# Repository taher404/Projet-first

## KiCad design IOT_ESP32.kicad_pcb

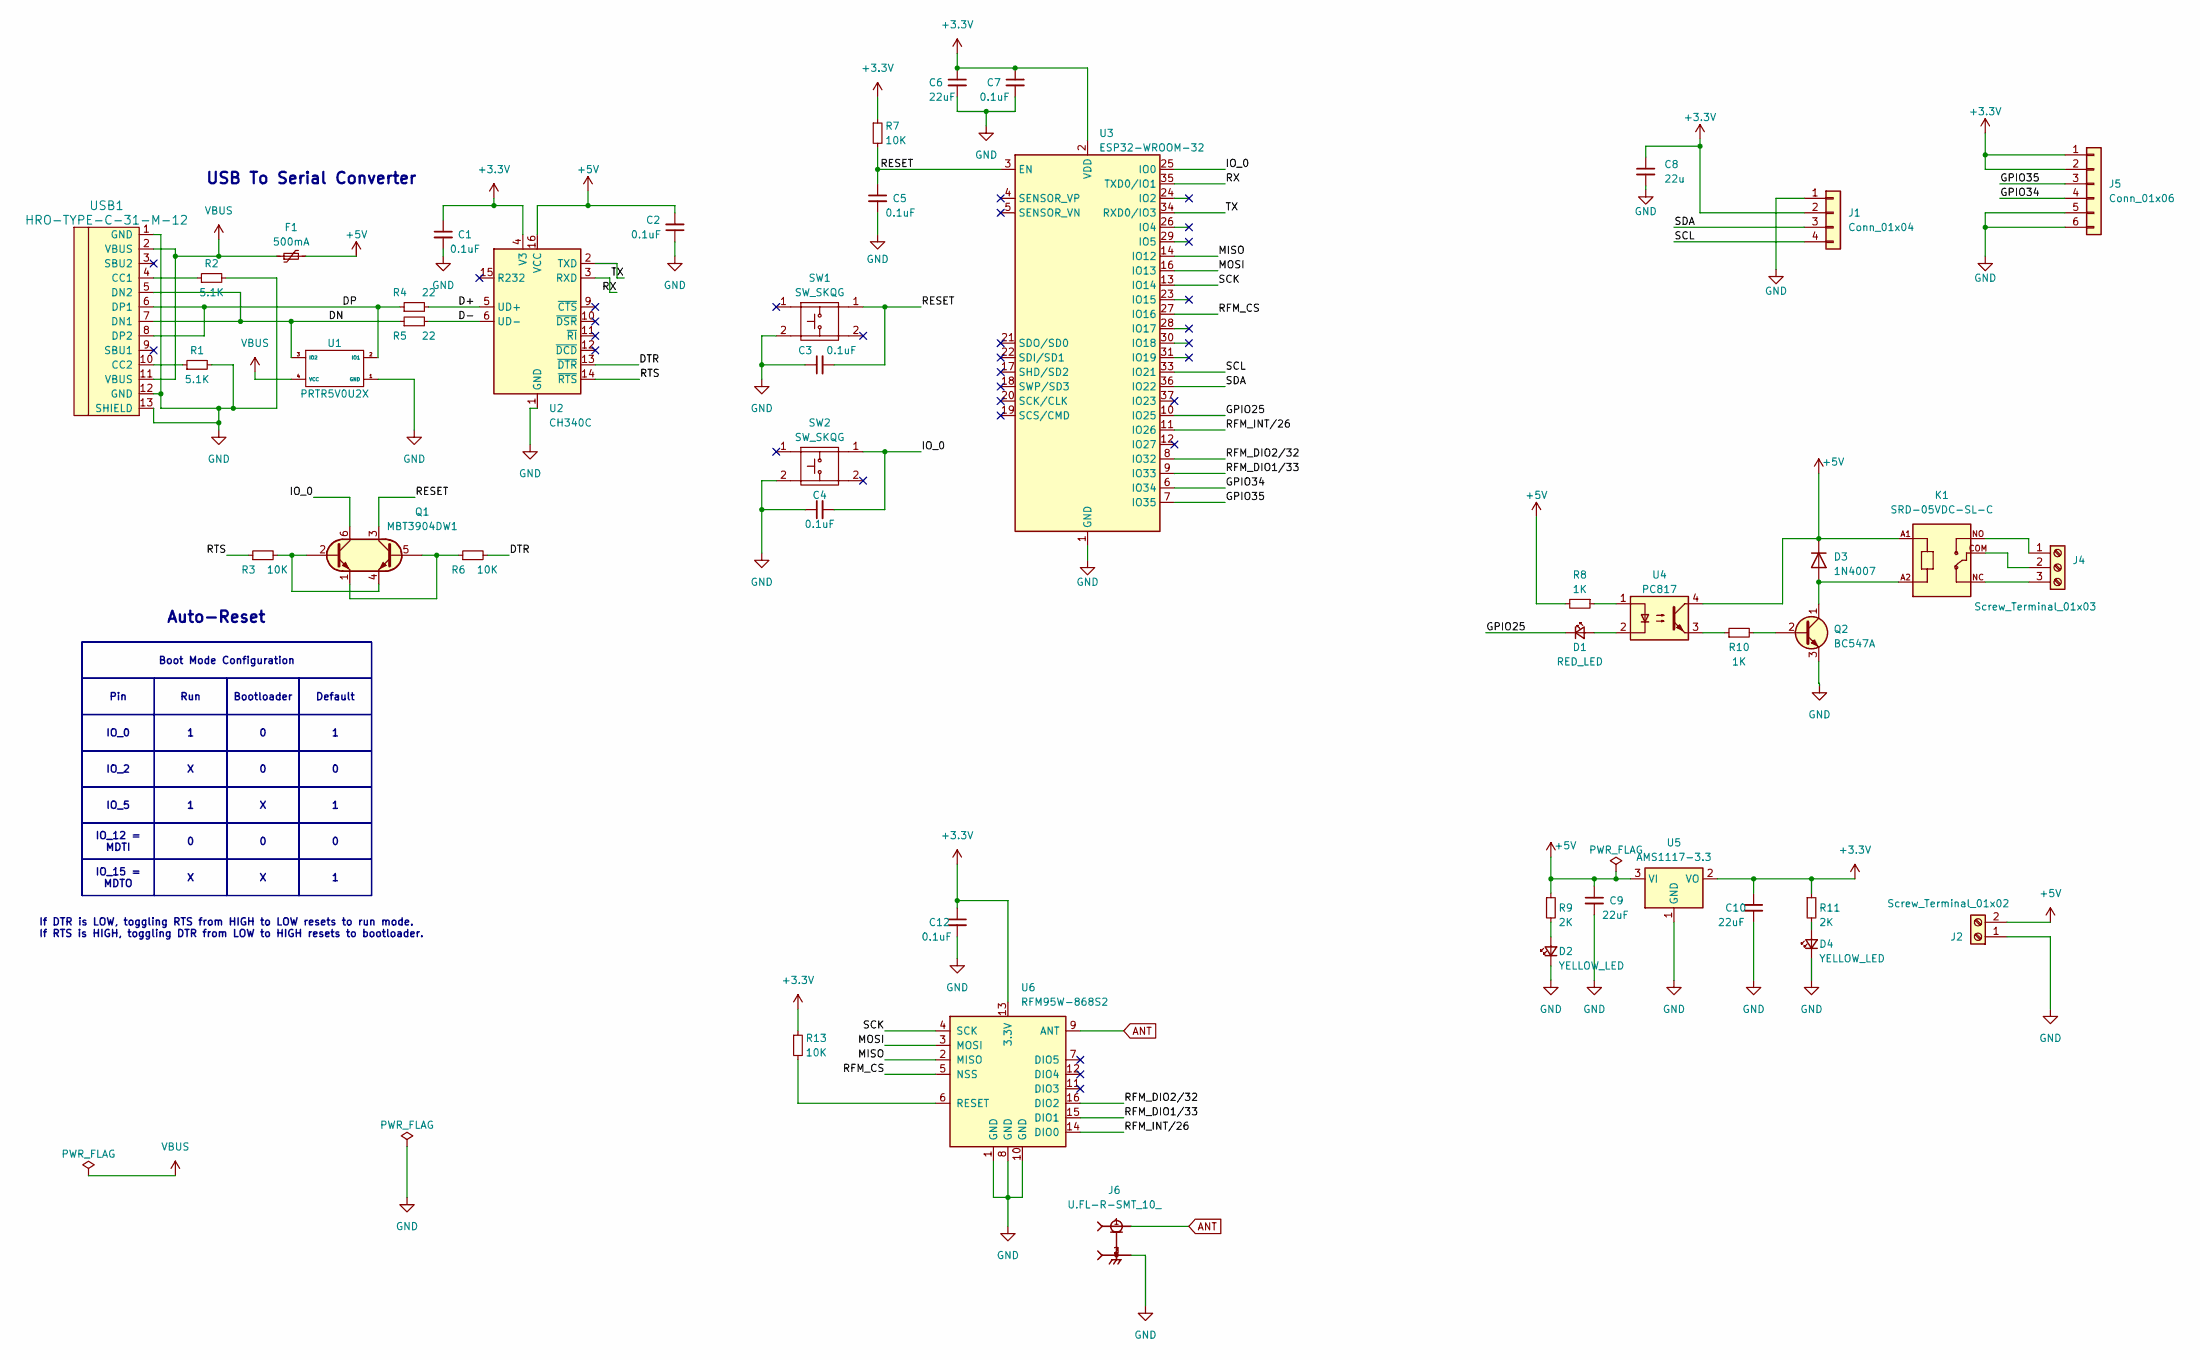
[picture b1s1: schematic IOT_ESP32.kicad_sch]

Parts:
C1, C2, C3, C4, C5, C7, C12: 0.1uF; C_0805_2012Metric_Pad1.18x1.45mm_HandSolder
C6, C9, C10: 22uF; C_0805_2012Metric_Pad1.18x1.45mm_HandSolder
C8: 22u; C_0805_2012Metric_Pad1.18x1.45mm_HandSolder
D1: RED_LED; LED_0805_2012Metric_Pad1.15x1.40mm_HandSolder
D2, D4: YELLOW_LED; LED_0805_2012Metric_Pad1.15x1.40mm_HandSolder
D3: 1N4007; D_DO-41_SOD81_P12.70mm_Horizontal
F1: 500mA; Fuse_1206_3216Metric_Pad1.42x1.75mm_HandSolder
J1: Conn_01x04; PinHeader_1x04_P2.54mm_Vertical
J2: Screw_Terminal_01x02; TerminalBlock_Phoenix_MKDS-1,5-2_1x02_P5.00mm_Horizontal
J4: Screw_Terminal_01x03; TerminalBlock_Phoenix_MKDS-1,5-3_1x03_P5.00mm_Horizontal
J5: Conn_01x06; PinHeader_1x06_P2.54mm_Vertical
J6: U.FL-R-SMT_10_; HRS_U.FL-R-SMT_10_
K1: SRD-05VDC-SL-C; RELAY_SRD-05VDC-SL-C
Q1: MBT3904DW1
Q2: BC547A
R1, R2: 5.1K; R_0805_2012Metric_Pad1.20x1.40mm_HandSolder
R3, R6, R7, R13: 10K; R_0805_2012Metric_Pad1.20x1.40mm_HandSolder
R4, R5: 22; R_0805_2012Metric_Pad1.20x1.40mm_HandSolder
R8, R10: 1K; R_0805_2012Metric_Pad1.20x1.40mm_HandSolder
R9, R11: 2K; R_0805_2012Metric_Pad1.20x1.40mm_HandSolder
SW1, SW2: SW_SKQG; SW_SPST_SKQG_WithStem
U1: PRTR5V0U2X; PRTR5VOU2X
U2: CH340C
U3: ESP32-WROOM-32
U4: PC817
U5: AMS1117-3.3
U6: RFM95W-868S2; XCVR_RFM95W-915S2
USB1: HRO-TYPE-C-31-M-12; HRO-TYPE-C-31-M-12-HandSoldering

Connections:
+3.3V: C1.1, C6.1, C7.1, C8.1, C10.1, C12.1, J1.2, J5.1, J5.2, R7.1, R11.1, R13.1, U2.4 (V3), U3.2 (VDD), U5.2 (VO), U6.13 (3.3V)
+5V: C2.2, C9.1, D3.1 (K), F1.2, J2.2, K1.A1, R8.2, R9.1, U2.16 (VCC), U4.4, U5.3 (VI)
/D+: R4.2, U2.5 (UD+)
/D-: R5.2, U2.6 (UD-)
/DN: R5.1, U1.3 (IO2), USB1.5 (DN2), USB1.7 (DN1)
/DP: R4.1, U1.2 (IO1), USB1.6 (DP1), USB1.8 (DP2)
/DTR: R6.2, U2.13 (~DTR)
/GPIO25: D1.1 (K), U3.10 (IO25)
/GPIO34: J5.4, U3.6 (IO34)
/GPIO35: J5.3, U3.7 (IO35)
/IO_0: C4.2, SW2.1
/IO_0: Q1.6 (C1), U3.25 (IO0)
/MISO: U3.14 (IO12), U6.2 (MISO)
/MOSI: U3.16 (IO13), U6.3 (MOSI)
/RESET: C3.2, C5.1, Q1.3 (C2), R7.2, SW1.1, U3.3 (EN)
/RFM_CS: U3.27 (IO16), U6.5 (NSS)
/RFM_DIO1/33: U3.9 (IO33), U6.15 (DIO1)
/RFM_DIO2/32: U3.8 (IO32), U6.16 (DIO2)
/RFM_INT/26: U3.11 (IO26), U6.14 (DIO0)
/RTS: R3.1, U2.14 (~RTS)
/RX: U2.3 (RXD), U3.35 (TXD0/IO1)
/SCK: U3.13 (IO14), U6.4 (SCK)
/SCL: J1.4, U3.33 (IO21)
/SDA: J1.3, U3.36 (IO22)
/TX: U2.2 (TXD), U3.34 (RXD0/IO3)
ANT: J6.1, U6.9 (ANT)
GND: C1.2, C2.1, C3.1, C4.1, C5.2, C6.2, C7.2, C8.2, C9.2, C10.2, C12.2, D2.1 (K), D4.1 (K), J1.1, J2.1, J5.5, J5.6, J6.2, J6.3, Q2.3 (E), R1.2, R2.2, SW1.2, SW2.2, U1.1 (GND), U2.1 (GND), U3.1 (GND), U3.15 (GND), U3.38 (GND), U3.39 (GND), U5.1 (GND), U6.1 (GND), U6.8 (GND), U6.10 (GND), USB1.1 (GND), USB1.12 (GND), USB1.13 (SHIELD)
unnamed: D1.2 (A), U4.2
unnamed: D2.2 (A), R9.2
unnamed: D3.2 (A), K1.A2, Q2.1 (C)
unnamed: D4.2 (A), R11.2
unnamed: J4.1, K1.NO
unnamed: J4.2, K1.COM
unnamed: J4.3, K1.NC
unnamed: Q1.2 (B1), Q1.4 (E2), R3.2
unnamed: Q1.1 (E1), Q1.5 (B2), R6.1
unnamed: Q2.2 (B), R10.2
unnamed: R8.1, U4.1
unnamed: R10.1, U4.3
unnamed: R13.2, U6.6 (RESET)
unnamed: R2.1, USB1.4 (CC1)
unnamed: R1.1, USB1.10 (CC2)
VBUS: F1.1, U1.4 (VCC), USB1.2 (VBUS), USB1.11 (VBUS)

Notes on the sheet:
Pin
Run
Default
Bootloader
IO_2
IO_5
IO_0
IO_15 = MDTO
IO_12 = MDTI
Boot Mode Configuration
USB To Serial Converter
Auto-Reset
If DTR is LOW, toggling RTS from HIGH to LOW resets to run mode. If RTS is HIGH, toggling DTR from LOW to HIGH resets to bootloader.

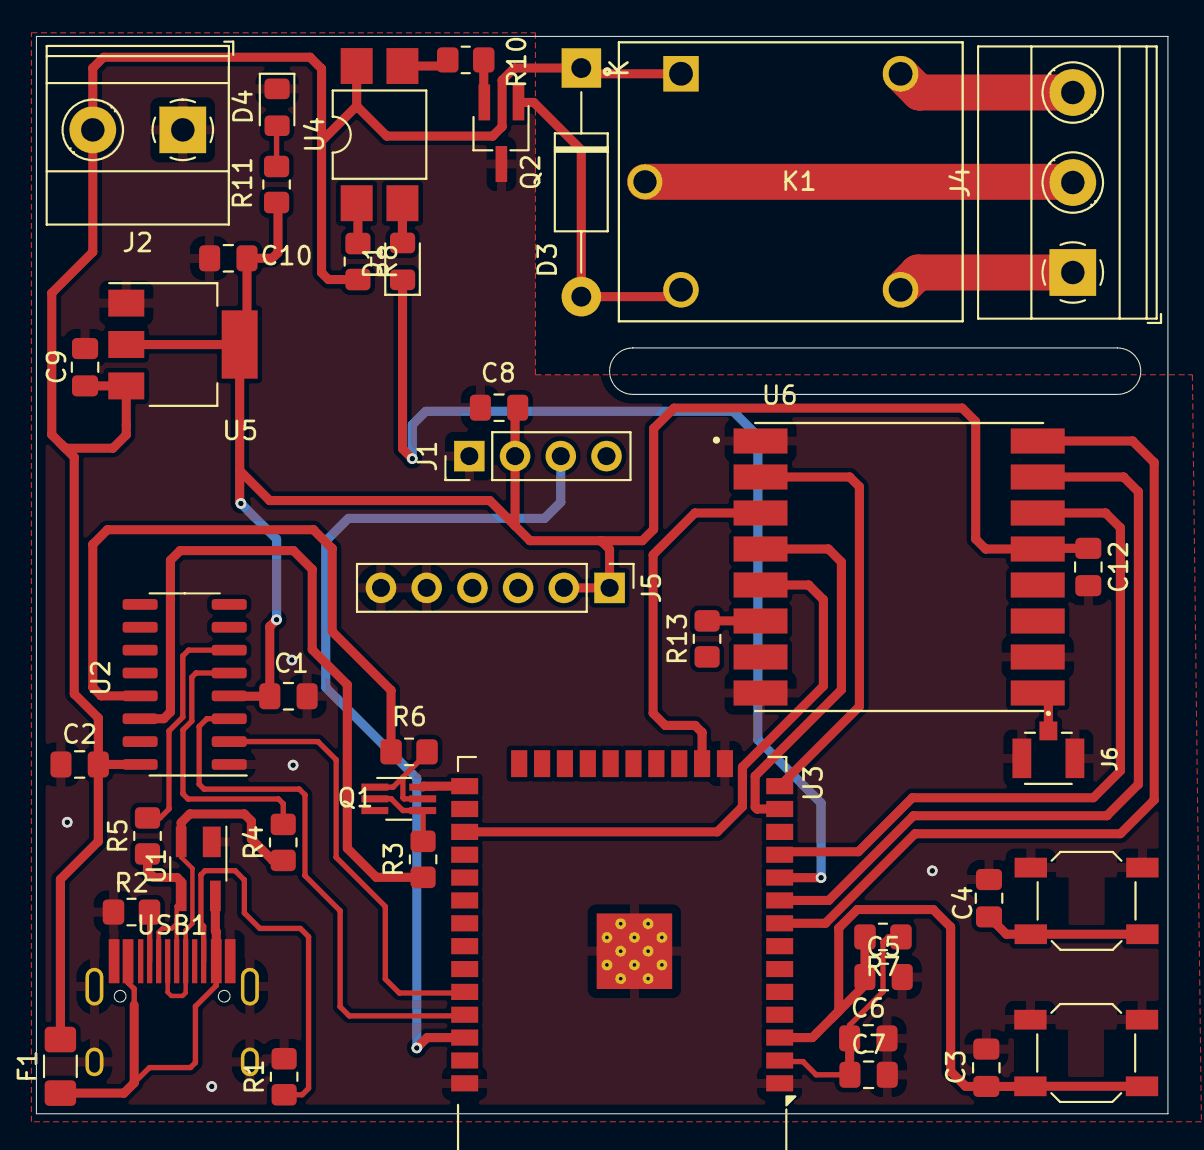
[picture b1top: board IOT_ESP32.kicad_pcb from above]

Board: 2 copper layers, 62.9 x 59.9 mm, 43 parts (0 on the bottom side), 42 nets.

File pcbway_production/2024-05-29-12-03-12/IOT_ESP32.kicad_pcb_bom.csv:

designator,quantity,value,pack,mpn,mount_type
"C1, C2, C3, C4, C5, C7",6,0.1uF,C_0805_2012Metric_Pad1.18x1.45mm_HandSolder,,smt
"C10, C6, C9",3,22uF,C_0805_2012Metric_Pad1.18x1.45mm_HandSolder,,smt
"C11, C12",2,4.7uF,C_0805_2012Metric_Pad1.18x1.45mm_HandSolder,,smt
C8,1,22u,C_0805_2012Metric_Pad1.18x1.45mm_HandSolder,,smt
D1,1,RED_LED,LED_0805_2012Metric_Pad1.15x1.40mm_HandSolder,,smt
"D2, D4",2,YELLOW_LED,LED_0805_2012Metric_Pad1.15x1.40mm_HandSolder,,smt
D3,1,1N4007,D_DO-41_SOD81_P12.70mm_Horizontal,,tht
F1,1,500mA,Fuse_1206_3216Metric_Pad1.42x1.75mm_HandSolder,,smt
J1,1,Conn_02x04_Top_Bottom,PinHeader_2x04_P2.54mm_Vertical,,tht
J2,1,Screw_Terminal_01x02,"TerminalBlock_Phoenix_MKDS-1,5-2_1x02_P5.00mm_Horizontal",,tht
J3,1,Conn_01x04,JST_XH_B4B-XH-A_1x04_P2.50mm_Vertical,,tht
J4,1,Screw_Terminal_01x03,"TerminalBlock_Phoenix_MKDS-1,5-3_1x03_P5.00mm_Horizontal",,tht
J6,1,U.FL-R-SMT_10_,HRS_U.FL-R-SMT_10_,,smt
K1,1,SRD-05VDC-SL-C,RELAY_SRD-05VDC-SL-C,,tht
Q1,1,MBT3904DW1,MBT3904DW1,,smt
Q2,1,BC547A,BC547A,,smt
"R1, R2",2,5.1K,R_0805_2012Metric_Pad1.20x1.40mm_HandSolder,,smt
"R10, R8",2,1K,R_0805_2012Metric_Pad1.20x1.40mm_HandSolder,,smt
"R11, R9",2,2K,R_0805_2012Metric_Pad1.20x1.40mm_HandSolder,,smt
"R12, R3, R6, R7",4,10K,R_0805_2012Metric_Pad1.20x1.40mm_HandSolder,,smt
"R4, R5",2,22,R_0805_2012Metric_Pad1.20x1.40mm_HandSolder,,smt
"SW1, SW2",2,SW_SKQG,SW_SPST_SKQG_WithStem,,smt
U1,1,PRTR5V0U2X,PRTR5VOU2X,,smt
U2,1,CH340C,CH340C,,smt
U3,1,ESP32-WROOM-32,ESP32-WROOM-32,,smt
U4,1,PC817,PC817,,smt
U5,1,AMS1117-3.3,AMS1117-3.3,,smt
U7,1,RFM95W-915S2,XCVR_RFM95W-915S2,,smt
USB1,1,HRO-TYPE-C-31-M-12,HRO-TYPE-C-31-M-12-HandSoldering,,smt

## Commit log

2024-05-29 first commit
    news project first with KiCad
